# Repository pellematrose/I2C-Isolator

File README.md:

## I2C Isolator with Power 
This is likely the smallest PCB that combines I2C and power isolation in a compact design. 
It delivers 1W of isolated output power, all within an extremely small form factor. 
It connects seamlessly to your microcontroller project using a STEMMA QT (JST SH 4-Pin) cable, ideal for isolating your sensor board.

## Use cases:
- Applications requiring electrical isolation
- Long wiring runs where signal integrity suffers
- Prevention of ground loops and noise

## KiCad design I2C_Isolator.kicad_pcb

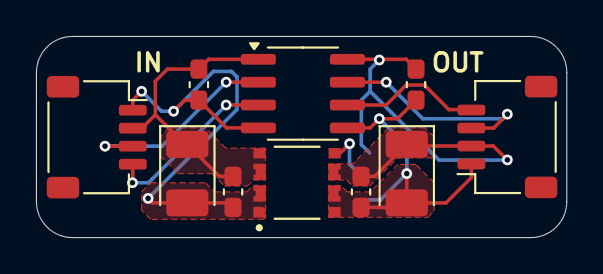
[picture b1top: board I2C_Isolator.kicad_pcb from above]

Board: 2 copper layers, 29.5 x 11.2 mm, 11 parts (1 on the bottom side), 9 nets.

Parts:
C1, C2, C4, C5: 100n; C_0603_1608Metric_Pad1.08x0.95mm_HandSolder
C3, C6: 22u; CP_EIA-3528-21_Kemet-B_Pad1.50x2.35mm_HandSolder
J5, J6: Conn_01x04_Socket; JST_SH_SM04B-SRSS-TB_1x04-1MP_P1.00mm_Horizontal
JP1: Jumper_3_Open; SolderJumper-3_P1.3mm_Open_RoundedPad1.0x1.5mm
U1: ISO1641B; SOIC-8_3.9x4.9mm_P1.27mm
U2: R05C1TF05S-R; CONV_R05C1TF05S-R

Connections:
+5V: C1.1, C3.1, C4.1, J6.2, U1.1 (VCC1), U2.4_5 (VIN+), U2.6 (CTRL)
+5Viso: C2.1, C5.1, C6.1, J5.2, JP1.1 (A), U1.8 (VCC2), U2.8_9 (VOUT+)
GND: C1.2, C3.2, C4.2, J6.1, U1.4 (GND1), U2.1 (VIN-), U2.2_3 (VIN-)
GNDiso: C2.2, C5.2, C6.2, J5.1, JP1.3 (B), U1.5 (GND2), U2.10_11 (VOUT-), U2.12 (VOUT-)
unnamed: JP1.2 (C), U2.7 (VSEL)
SCK1: J6.4, U1.3 (SCL1)
SCK1iso: J5.4, U1.6 (SCL2)
SDA1: J6.3, U1.2 (SDA1)
SDA1iso: J5.3, U1.7 (SDA2)
